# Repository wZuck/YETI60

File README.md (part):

English | [Chinese](README.zh-CN.md)

# YETI60

> **Active prototype: Raytac MDBT50Q-1MV2.** Start at [START-HERE.md](START-HERE.md) or the [ordering and build handbook](variants/raytac/BUILD.md) for PCB settings, inventory-adjusted materials, soldering, firmware, complete explosion and current review. E73 remains a separate option; see its [current review and build entry](BUILD.md) before using those files. Physical and supplier acceptance remain open.

A single-nRF52840 electrocapacitive keyboard PCB for the FELK60 case, derived from Cipulot EC60. The 60 effective sensing positions and mounts are retained. Raytac retains its RF wing; the E73 corner candidate restores the straight edge and front-mounts the module. C5 feeds USB through J4, with a J5/J1 power bridge.

**Wired operation:** after a computer accepts the USB configuration, the keyboard charges the battery and sends HID input over USB at the same time. USB automatically takes priority over a retained Bluetooth preference; unplugging lets ZMK fall back to the active Bluetooth profile. The E73 and Raytac options use the same policy. The 500 mA descriptor is an input budget, not a constant battery charging current.

> **P2 design checkpoint:** C5 JSH is retained. The default is now a custom 1600 mAh single-cell pack with a canonical recessed bottom, revised charger settings and USB500 firmware. Engineering sheets, PCB animation and assembly renders record their source hashes. See [checkpoint details](docs/design-checkpoint.md).

> **Acceptance hold:** E73 is now in the lower-right HHKB corner. Strict DRC has zero violation errors but zero unconnected items; earlier zero-open and firmware reports do not qualify this placement. See the [current migration review](docs/engineering/e73-hhkb-corner.md). Raytac has a separate [review](variants/raytac/BUILD.md). Neither is a production release.

## Current review

**The E73 corner version has completed native routing; whole-board acceptance remains open.** Start at [BUILD.md](BUILD.md). The results below describe the [corner candidate](docs/engineering/e73-hhkb-corner.md); earlier upper-right acceptance does not transfer.

| Scope | Current evidence and result |
|---|---|
| PCB | Strict DRC: 0 violation errors, zero unconnected items, 0 schematic-parity differences; 60 effective sensing positions and 43 module pad roles retained; fabrication remains on hold |
| Firmware | [Candidate normal/calibrator images and manifest](hardware/e73-hhkb-corner/firmware/manifest.json) rebuilt for this PCB; linked-target and host suite passed; physical tests remain open |
| Mechanical | NiZ, the 1.6 mm steel plate and 28 mounting sets retained; module/local body bounds passed, complete mechanism and harness motion still open |
| Battery | Protected 1S 1600 mAh, complete 85 × 43 × 4.8 mm envelope retained; mainboard uses a three-pin SH connector; supplier parameters and independent thermal protection remain open |
| Visualization | [Current native PCB placement](hardware/e73-hhkb-corner/audit/corner-layout.png); old 28-step guide and complete renders are pre-migration references, not this revision's assembly proof |

The remaining study and step-guide links below retain pre-migration reference records; use the corner reports above for this revision.

- [Internal connections and cable drawing](docs/engineering/interconnects.md)
- [Feasibility assessment response](docs/engineering/assessment-response.md)
- [Ordinary fabrication review package](docs/engineering/fabrication-review.md)
- [Engineering assembly sheets and sequence](docs/engineering/assembly.md)
- [28-step illustrated soldering and installation guide](docs/assembly/build-guide.md)
- [Battery recess feasibility](docs/engineering/battery-study.md)
- [Power, runtime and charging calculation](docs/engineering/power-budget.md)
- [Materials and procurement table](docs/engineering/materials.md)
- [PCB marking cleanup](docs/engineering/board-markings.md)
- [Complete review](docs/audit/yeti60-comprehensive-review.md)
- [Hardware and fabrication notes](hardware/ec60-nrf52840/README.md)
- [Firmware core, simulation and trace](firmware/yeti60/README.md)
- [Assembly renders](renders/yeti60-assembly/README.md)
- [PCB renders and 360° animation](renders/ec60-nrf52840/README.md)
- [Current audit index](docs/audit/README.md)

The case material is provisionally resin. SI/RF screening has started; antenna layout blockers and physical qualification remain open. Project-owned prose defaults to English with a parallel `.zh-CN.md`; machine-readable field names stay stable.

Based on [Cipulot/EC60](https://github.com/Cipulot/EC60) and [fredlb/felk60](https://github.com/fredlb/felk60). Upstream authors, licenses and original project names are retained. Existing `EC60-nRF52840.*` filenames and `YAECKB` library identifiers remain for technical compatibility; the public project name is **YETI60**.

## Complete materials for one keyboard

**E73 design hold:** the list below now uses NiZ, a 1.6 mm plate and 28 mounting sets. USB routing and PH connector service remain unresolved, so mainboard manufacturing is still on hold. Read the [current E73 entry](BUILD.md) first; use the [separate Raytac list](variants/raytac/BUILD.md) for that candidate. Retain the already-made C5 daughterboard.

Quantities below are **net installed quantities for one complete keyboard, without spares**. Buy populated mainboard/daughterboard assemblies or their loose parts; do not count the same components twice. Unselected suppliers/MPNs are identified explicitly. A known quantity does not constitute procurement release.

**Fabrication constraint: JLC ordinary four-layer FR-4 only. The previous blind-via/filled-and-capped design has been converted to mechanically drilled through vias; do not order the old HDI files.** Use the latest fabrication review after conversion. No second controller, per-key diodes or MX hot-swap sockets are required.

### Use existing inventory first

The supplied order-derived inventory covers **8** of the 75 current corner mainboard parts by nominal value/package, leaving **67** to purchase for one keyboard. Count the actual unused stock and qualify capacitor effective capacitance before assembly. In-transit items are excluded. The original workbook is unchanged and is not published.

| Stock MPN | References | Planned use |
|---|---|---:|
| Samsung CL05B104KO5NNNC, 100 nF / 16 V / X7R / 0402 | C9, C11, C12, C31 | 4 |
| Samsung CL05A105KA5NQNC, 1 uF / 25 V / X5R / 0402 | C13, C48 | 2 |
| Uniroyal 0402WGF1001TCE, 1 kohm / 1% / 0402 | R17 | 1 |
| Uniroyal 0402WGF1002TCE, 10 kohm / 1% / 0402 | R26 | 1 |

Use the [stock-adjusted mainboard purchase CSV](hardware/e73-hhkb-corner/mainboard-purchase.csv) and [inventory decisions](docs/engineering/inventory-allocation.md) alongside the full preparation list below. Other assemblies and mechanical materials still require procurement or compatibility confirmation. A populated C5 includes its seven parts; if self-assembling a bare C5 instead, two stocked 5.1 kohm resistors can supply C5 R1/R2. The stock nice!nano, 110 mAh cell, 0805 capacitors and short PCB screws do not directly replace the specified parts. No board or case dimensions change for this allocation.

### Which PCBs to fabricate

Quantities are net boards per keyboard; the fabricator's minimum order quantity is separate. Fabricate **one mainboard** when buying a populated C5, or **one mainboard plus one C5 JSH bare board** when soldering the daughterboard yourself.

| PCB | Quantity | Specification | Files |
|---|---:|---|---|
| YETI60 E73 mainboard | 1 | 285.0 × 94.6 mm restored straight-edge outline; JLC ordinary four-layer FR-4, nominal 1.6 mm, through vias only | [Current KiCad PCB](hardware/e73-hhkb-corner/EC60-nRF52840.kicad_pcb), [migration gates](docs/engineering/e73-hhkb-corner.md); no fabrication package released for this revision; do not substitute old Gerbers |
| Unified Daughterboard C5 JSH | 1 only for self-assembly; 0 if purchased populated | 18.0 x 16.5 mm; **four layers**, nominal 1.6 mm, ordinary through vias; 14 x 12.5 mm mounting rectangle | [Pinned upstream KiCad PCB](https://github.com/Unified-Daughterboard/UDB-C-JSH/blob/2b6c52aa2de6f9f60ca99c6250e4bdf01e8f4eea/UDB.kicad_pcb), [download pinned Gerber/drill ZIP](https://raw.githubusercontent.com/Unified-Daughterboard/UDB-C-JSH/2b6c52aa2de6f9f60ca99c6250e4bdf01e8f4eea/production/UDB-C-JSH_5.0_gerbers.zip), [seven loose parts](hardware/bom/daughterboard.csv) |

No fabrication package is released for this corner mainboard. Do not substitute an old mainboard archive. C5 uses separate, unchanged four-layer files; do not order it as two layers. Reuse the already-made C5. Final stencil and supplier acceptance remain open. J3 is part of the main PCB and needs a pogo fixture, not another PCB in this design. The stainless plate, resin shells and five routing guides are mechanical parts, not additional PCBs. For self-reflow, use mainboard **F.Paste and B.Paste** (E73 on front, other parts on back) and C5 **F.Paste** with a qualified stencil/profile.

### Electronic assemblies, battery and cables

| Material | Quantity | Detailed specification and included items |
|---|---:|---|
| Mainboard PCB | 1 | Current YETI60 native PCB; ordinary four-layer FR-4, target nominal thickness 1.6 mm; preserve EC electrodes and mounting centers; use the restored straight right edge; CAD envelope 1.6062 mm; wait for this revision to be released with matching fabrication files |
| Mainboard fitted parts | 75 | Every reference, value, package and specified/candidate MPN is listed below; included if buying a populated mainboard |
| USB daughterboard | 1 populated | Unified Daughterboard C5 JSH, commit `2b6c52a`; seven fitted components including USB-C receptacle and SH header; retain C rather than S |
| Internal USB harness | 1 four-wire | AWG28 stranded copper, insulation OD ≤0.8 mm; two SHR-04V-S housings and eight SSH-003T-P0.2-H contacts; C5 to J4: 1-to-1 power, 2-to-2 D−, 3-to-3 D+, 4-to-4 GND. Complete new routing remains unqualified; do not cut to the old 150 mm figure |
| J5-to-J1 power bridge | 1 two-wire | AWG28, insulation OD ≤0.8 mm; one SHR-02V-S, one SHR-04V-S and four SSH-003T-P0.2-H contacts; J5.1→J1.1 and J5.2→J1.4, J1.2/J1.3 empty; final lengths and retention remain open |
| Battery assembly | 1 pack | Custom single-cell YETI60-BAT-1600-1S, target minimum 1600 mAh; complete pack <=85 x 43 x 4.8 mm including PCM, sensors, wrap, tabs and growth; independent thermal interruption, actual charging window within 15–43 C; supplier must accept >=500 mA continuous charging capability and the 4.16–4.23 V regulation range |
| Battery leads and plug | 1 three-wire set, included in pack | AWG28, OD <=0.8 mm; one SHR-03V-S housing and three SSH-003T-P0.2-H contacts, mating with SM03B-SRSS-TB at 1.00 mm pitch; pin 1 red positive, 2 black negative, 3 yellow separate 10k NTC. Independent thermal protection and third-wire NTC feedback are separate requirements; supplier-signed envelope/lead-exit drawing required |
| External USB data cable | 1 | USB-C at keyboard; USB-A or USB-C at host as appropriate; data capable, not charge-only |

### Every fitted mainboard component

0402 resistors: 1%, >=50 mW; fit 0-ohm links where specified. The 220 pF capacitor is C0G; others X5R/X7R, 10% or better, >=10 V (16 V where specified), with effective DC-biased capacitance to be qualified. Values below are current circuit requirements; unselected MPNs are not frozen parts.

| References | Quantity | Value/function | Package | Specified/candidate MPN | Planned stock | To buy | Stock and qualification notes |
|---|---:|---|---|---|---:|---:|---|
| C9, C11, C12 | 3 | 100n | C_0402_1005Metric | Samsung CL05B104KO5NNNC | 3 | 0 | In inventory: Samsung CL05B104KO5NNNC; recorded received pool 100 (shared by source row, do not sum per BOM row); count before assembly; qualify effective capacitance |
| C10 | 1 | 220p | C_0402_1005Metric | Vendor MPN unselected | 0 | 1 | No matched usable stock; purchase required |
| C13 | 1 | 1u | C_0402_1005Metric | Samsung CL05A105KA5NQNC | 1 | 0 | In inventory: Samsung CL05A105KA5NQNC; recorded received pool 50 (shared by source row, do not sum per BOM row); count before assembly; qualify effective capacitance |
| C30 | 1 | 10u/10V | C_0603_1608Metric | Vendor MPN unselected | 0 | 1 | No matched usable stock; purchase required |
| C41 | 1 | 22u/10V | C_0805_2012Metric | Vendor MPN unselected | 0 | 1 | No matched usable stock; purchase required; 0805 X5R/X7R; require effective capacitance >= 4.7 uF at 4.23 V including tolerance/temperature/aging; nominal value alone is insufficient. Installed height below local PCB underside <= 1.6 mm including solder/seating; body and placement XY growth <= 0.1 mm per direction; remaining tolerances in local fit guide. |
| C42 | 1 | 22u/10V | C_0805_2012Metric | Vendor MPN unselected | 0 | 1 | No matched usable stock; purchase required; 0805 X5R/X7R; require effective capacitance >= 4.7 uF at 4.5 V including tolerance/temperature/aging; nominal value alone is insufficient. Installed height below local PCB underside <= 1.6 mm including solder/seating; body and placement XY growth <= 0.1 mm per direction; remaining tolerances in local fit guide. |
| C43 | 1 | 22u/10V | C_0805_2012Metric | Vendor MPN unselected | 0 | 1 | No matched usable stock; purchase required; 0805 X5R/X7R; require effective capacitance >= 4.7 uF at 4.5 V including tolerance/temperature/aging; nominal value alone is insufficient. Installed height below local PCB underside <= 1.6 mm including solder/seating; body and placement XY growth <= 0.1 mm per direction; remaining tolerances in local fit guide. |
| C45 | 1 | 22u/10V | C_0805_2012Metric | Vendor MPN unselected | 0 | 1 | No matched usable stock; purchase required; 0805 X5R/X7R; require effective capacitance >= 5 uF at 3.6 V including tolerance/temperature/aging; nominal value alone is insufficient. Installed height below local PCB underside <= 1.6 mm including solder/seating; body and placement XY growth <= 0.1 mm per direction; remaining tolerances in local fit guide. |
| C46 | 1 | 22u/10V | C_0805_2012Metric | Vendor MPN unselected | 0 | 1 | No matched usable stock; purchase required; 0805 X5R/X7R; require effective capacitance >= 5 uF at 3.6 V including tolerance/temperature/aging; nominal value alone is insufficient. Installed height below local PCB underside <= 1.6 mm including solder/seating; body and placement XY growth <= 0.1 mm per direction; remaining tolerances in local fit guide. |
| C31 | 1 | 100n/16V | C_0402_1005Metric | Samsung CL05B104KO5NNNC | 1 | 0 | In inventory: Samsung CL05B104KO5NNNC; recorded received pool 100 (shared by source row, do not sum per BOM row); count before assembly; qualify effective capacitance |
| C32 | 1 | 4.7u/16V | C_0603_1608Metric | Vendor MPN unselected | 0 | 1 | No matched usable stock; purchase required; 0603 X5R/X7R; require effective capacitance >= 2.2 uF at 5.25 V including tolerance/temperature/aging; nominal value alone is insufficient. Installed height below local PCB underside <= 1 mm including solder/seating; body and placement XY growth <= 0.1 mm per direction; remaining tolerances in local fit guide. |
| C40 | 1 | 2.2u/25V | C_0805_2012Metric | Vendor MPN unselected | 0 | 1 | No matched usable stock; purchase required; 0805 X5R/X7R; require effective capacitance >= 1 uF at 5.25 V including tolerance/temperature/aging; nominal value alone is insufficient. Installed height below local PCB underside <= 1.6 mm including solder/seating; body and placement XY growth <= 0.1 mm per direction; remaining tolerances in local fit guide. |
| C44 | 1 | 100n/16V | C_0603_1608Metric | Vendor MPN unselected | 0 | 1 | No matched usable stock; purchase required. Installed height below local PCB underside <= 1 mm including solder/seating; body and placement XY growth <= 0.1 mm per direction; remaining tolerances in local fit guide. |
| C47 | 1 | 10n | C_0402_1005Metric | Vendor MPN unselected | 0 | 1 | No matched usable stock; purchase required |
| C48 | 1 | 1u/10V | C_0402_1005Metric | Samsung CL05A105KA5NQNC | 1 | 0 | In inventory: Samsung CL05A105KA5NQNC; recorded received pool 50 (shared by source row, do not sum per BOM row); count before assembly; qualify effective capacitance |
| D2 | 1 | STATUS | LED_0603_1608Metric | 0603 status LED; vendor MPN unselected | 0 | 1 | No matched usable stock; purchase required |
| F1 | 1 | 1A_FAST_0466001_NRHF | Fuse_Littelfuse_0466_1206 | Littelfuse 0466001.NRHF (1 A fast, not resettable) | 0 | 1 | No matched usable stock; purchase required. Installed height below local PCB underside <= 1.2 mm including solder/seating; body and placement XY growth <= 0.1 mm per direction; remaining tolerances in local fit guide. |
| J1 | 1 | USB_POWER_IN | JST-SR-4 | JST SM04B-SRSS-TB(LF)(SN), candidate | 0 | 1 | No matched usable stock; purchase required |
| J2 | 1 | PROTECTED_1S_4V2_NTC10K | JST SH 1.0 mm side-entry 3-pin | JST SM03B-SRSS-TB(LF)(SN) | 0 | 1 | No matched usable stock; purchase required; SH3 revision: protected PACK+/PACK-/NTC on pins 1/2/3; housing SHR-03V-S. Installed height below local PCB underside <= 3.2 mm including solder/seating; body and placement XY growth <= 0.1 mm per direction; remaining tolerances in local fit guide. |
| L1 | 1 | 1.5uH_74438336015 | WE-MAPI 3020, 3.0 x 3.0 x 2.0 mm | Wuerth 74438336015 | 0 | 1 | No matched usable stock; purchase required. Installed height below local PCB underside <= 2.2 mm including solder/seating; body and placement XY growth <= 0.1 mm per direction; remaining tolerances in local fit guide. |
| R3 | 1 | 100 | R_0402_1005Metric | Vendor MPN unselected | 0 | 1 | No matched usable stock; purchase required |
| R4 | 1 | 100 | R_0402_1005Metric | Vendor MPN unselected | 0 | 1 | No matched usable stock; purchase required |
| R5 | 1 | 100 | R_0402_1005Metric | Vendor MPN unselected | 0 | 1 | No matched usable stock; purchase required |
| R6 | 1 | 100 | R_0402_1005Metric | Vendor MPN unselected | 0 | 1 | No matched usable stock; purchase required |
| R7 | 1 | 100 | R_0402_1005Metric | Vendor MPN unselected | 0 | 1 | No matched usable stock; purchase required |
| R47 | 1 | 100 | R_0402_1005Metric | Vendor MPN unselected | 0 | 1 | No matched usable stock; purchase required. Installed height below local PCB underside <= 0.6 mm including solder/seating; body and placement XY growth <= 0.1 mm per direction; remaining tolerances in local fit guide. |
| R53 | 1 | 100 | R_0402_1005Metric | Vendor MPN unselected | 0 | 1 | No matched usable stock; purchase required |
| R54 | 1 | 100 | R_0402_1005Metric | Vendor MPN unselected | 0 | 1 | No matched usable stock; purchase required |
| R8 | 1 | 100k | R_0402_1005Metric | Vendor MPN unselected | 0 | 1 | No matched usable stock; purchase required |
| R9 | 1 | 100k | R_0402_1005Metric | Vendor MPN unselected | 0 | 1 | No matched usable stock; purchase required |
| R10 | 1 | 100k | R_0402_1005Metric | Vendor MPN unselected | 0 | 1 | No matched usable stock; purchase required |
| R11 | 1 | 100k | R_0402_1005Metric | Vendor MPN unselected | 0 | 1 | No matched usable stock; purchase required |
| R12 | 1 | 100k | R_0402_1005Metric | Vendor MPN unselected | 0 | 1 | No matched usable stock; purchase required |
| R13 | 1 | 100k | R_0402_1005Metric | Vendor MPN unselected | 0 | 1 | No matched usable stock; purchase required |
| R14 | 1 | 100k | R_0402_1005Metric | Vendor MPN unselected | 0 | 1 | No matched usable stock; purchase required |
| R15 | 1 | 100k | R_0402_1005Metric | Vendor MPN unselected | 0 | 1 | No matched usable stock; purchase required |
| R16 | 1 | 100k | R_0402_1005Metric | Vendor MPN unselected | 0 | 1 | No matched usable stock; purchase required |
| R18 | 1 | 100k | R_0402_1005Metric | Vendor MPN unselected | 0 | 1 | No matched usable stock; purchase required |
| R19 | 1 | 100k | R_0402_1005Metric | Vendor MPN unselected | 0 | 1 | No matched usable stock; purchase required |
| R20 | 1 | 100k | R_0402_1005Metric | Vendor MPN unselected | 0 | 1 | No matched usable stock; purchase required |
| R21 | 1 | 100k | R_0402_1005Metric | Vendor MPN unselected | 0 | 1 | No matched usable stock; purchase required |
| R23 | 1 | 100k | R_0402_1005Metric | Vendor MPN unselected | 0 | 1 | No matched usable stock; purchase required |
| R24 | 1 | 100k | R_0402_1005Metric | Vendor MPN unselected | 0 | 1 | No matched usable stock; purchase required |
| R25 | 1 | 100k | R_0402_1005Metric | Vendor MPN unselected | 0 | 1 | No matched usable stock; purchase required |
| R42 | 1 | 100k | R_0402_1005Metric | Vendor MPN unselected | 0 | 1 | No matched usable stock; purchase required |
| R43 | 1 | 100k | R_0402_1005Metric | Vendor MPN unselected | 0 | 1 | No matched usable stock; purchase required |
| R44 | 1 | 100k | R_0402_1005Metric | Vendor MPN unselected | 0 | 1 | No matched usable stock; purchase required |
| R45 | 1 | 100k | R_0402_1005Metric | Vendor MPN unselected | 0 | 1 | No matched usable stock; purchase required. Installed height below local PCB underside <= 0.6 mm including solder/seating; body and placement XY growth <= 0.1 mm per direction; remaining tolerances in local fit guide. |
| R46 | 1 | 100k | R_0402_1005Metric | Vendor MPN unselected | 0 | 1 | No matched usable stock; purchase required. Installed height below local PCB underside <= 0.6 mm including solder/seating; body and placement XY growth <= 0.1 mm per direction; remaining tolerances in local fit guide. |
| R48 | 1 | 100k | R_0402_1005Metric | Vendor MPN unselected | 0 | 1 | No matched usable stock; purchase required |
| R49 | 1 | 100k | R_0402_1005Metric | Vendor MPN unselected | 0 | 1 | No matched usable stock; purchase required |
| R50 | 1 | 100k | R_0402_1005Metric | Vendor MPN unselected | 0 | 1 | No matched usable stock; purchase required |
| R17 | 1 | 1k | R_0402_1005Metric | Uniroyal 0402WGF1001TCE | 1 | 0 | In inventory: Uniroyal 0402WGF1001TCE; recorded received pool 100 (shared by source row, do not sum per BOM row); count before assembly |
| R26 | 1 | 10k | R_0402_1005Metric | Uniroyal 0402WGF1002TCE | 1 | 0 | In inventory: Uniroyal 0402WGF1002TCE; recorded received pool 100 (shared by source row, do not sum per BOM row); count before assembly |
| R32 | 1 | 2.2k | R_0402_1005Metric | Vendor MPN unselected | 0 | 1 | No matched usable stock; purchase required |
| R40 | 1 | 2.21k/1% | R_0402_1005Metric | Vendor MPN unselected | 0 | 1 | No matched usable stock; purchase required |
| R41 | 1 | 7.50k/1% | R_0402_1005Metric | Vendor MPN unselected | 0 | 1 | No matched usable stock; purchase required |
| R51, R52 | 2 | 1M/1% | R_0402_1005Metric | Vendor MPN unselected | 0 | 2 | No matched usable stock; purchase required |
| R55 | 1 | 69.8k/1% | R_0402_1005Metric | Vendor MPN unselected | 0 | 1 | No matched usable stock; purchase required |
| R56 | 1 | 1.69k/1% | R_0402_1005Metric | Vendor MPN unselected | 0 | 1 | No matched usable stock; purchase required |
| SW1 | 1 | EVQPUC02K_RESET | Panasonic_EVQPUL_EVQPUC | Panasonic EVQPUC02K | 0 | 1 | No matched usable stock; purchase required |
| SW100 | 1 | JS102011SAQN_POWER | SW_SPDT_CK_JS102011SAQN | C&K JS102011SAQN | 0 | 1 | No matched usable stock; purchase required |
| U1 | 1 | E73-2G4M08S1C | E73-2G4M08S1C | Ebyte E73-2G4M08S1C | 0 | 1 | No matched usable stock; purchase required |
| U2, U4 | 2 | 74HC4051 | TSSOP16 | Nexperia 74HC4051PW,118 | 0 | 2 | No matched usable stock; purchase required |
| U3 | 1 | OPA350 | SOIC-8_3.9x4.9mm_P1.27mm | TI OPA350UA | 0 | 1 | No matched usable stock; purchase required |
| U5 | 1 | BQ24074RGT | VQFN-16-1EP_3x3mm_P0.5mm_EP1.6x1.6mm | TI BQ24074RGTR | 0 | 1 | No matched usable stock; purchase required. Installed height below local PCB underside <= 1.2 mm including solder/seating; body and placement XY growth <= 0.1 mm per direction; remaining tolerances in local fit guide. |
| U6 | 1 | TPS63031DSK | WSON-10-1EP_2.5x2.5mm_P0.5mm_EP1.2x2mm | TI TPS63031DSKR | 0 | 1 | No matched usable stock; purchase required. Installed height below local PCB underside <= 1 mm including solder/seating; body and placement XY growth <= 0.1 mm per direction; remaining tolerances in local fit guide. |
| U7, U8 | 2 | TPS22919DCK | SOT-363_SC-70-6 | TI TPS22919DCKR | 0 | 2 | No matched usable stock; purchase required |
| J4 | 1 | USB_C5_INPUT | JST SH 1.0 mm side-entry 4-pin | JST SM04B-SRSS-TB(LF)(SN) | 0 | 1 | No inventory credit; USB repair candidate, fabrication release still on hold. Installed height below local PCB underside <= 3.2 mm including solder/seating; body and placement XY growth <= 0.1 mm per direction; remaining tolerances in local fit guide. |
| J5 | 1 | USB_POWER_OUT | JST SH 1.0 mm side-entry 2-pin | JST SM02B-SRSS-TB(LF)(SN) | 0 | 1 | No inventory credit; USB repair candidate, fabrication release still on hold. Installed height below local PCB underside <= 3.2 mm including solder/seating; body and placement XY growth <= 0.1 mm per direction; remaining tolerances in local fit guide. |

### Optional: solder a bare C5 JSH daughterboard

Prepare **one bare C5 JSH PCB and the seven parts below** instead of buying a populated C5. [Local stock-adjusted CSV](hardware/bom/daughterboard.csv) · [Pinned upstream BOM](https://github.com/Unified-Daughterboard/UDB-C-JSH/blob/2b6c52aa2de6f9f60ca99c6250e4bdf01e8f4eea/production/UDB-C-JSH_5.0_bom.csv) · [Pinned upstream Gerber archive](https://github.com/Unified-Daughterboard/UDB-C-JSH/blob/2b6c52aa2de6f9f60ca99c6250e4bdf01e8f4eea/production/UDB-C-JSH_5.0_gerbers.zip).

| References | Quantity | Manufacturer and specified MPN | Package / connector footprint | LCSC code | Planned stock use | To buy | Inventory note |
| --- | --- | --- | --- | --- | --- | --- | --- |
| D1 | 1 | FTR SMF6.0A | SOD-123FL | C708002 | 0 | 1 | No matched usable stock; purchase required |
| F1 | 1 | Shenzhen JDT Fuse ASMD1206-150 | F1206 | C135342 | 0 | 1 | No matched usable stock; purchase required |
| J2 | 1 | JST SM04B-SRSS-TB(LF)(SN) | SM04B-SRSS-TB(LF)(SN)_mounting-reliefs | C160404 | 0 | 1 | No matched usable stock; purchase required |
| J1 | 1 | Korean Hroparts TYPE-C-31-M-12 | TYPE-C-31-M-12 | C165948 | 0 | 1 | 6 domestic substitutes recorded received; geometry/pinout unconfirmed, no credit |
| R1, R2 | 2 | Uniroyal 0402WGF5101TCE | R0402 | C25905 | 2 | 0 | Matching stock; recorded received pool 100, plan to use 2; count before assembly |
| U1 | 1 | Texas Instruments TPD4E05U06DQAR | uSON-10 | C138714 | 0 | 1 | No matched usable stock; purchase required |

The stock 5.1 kohm resistors cover R1/R2, so this option needs **five more loose parts plus one bare PCB**. The stock domestic TYPE-C-31-M-12 is not credited until its geometry is confirmed. These are daughterboard reference numbers, separate from mainboard references. The USB harness, four M2 screws and washers are separate assembly items below. LCSC codes identify the pinned upstream entries, not current prices or stock guarantees. BOM data: Copyright (c) 2023 Unified Daughterboard Project, [MIT license](hardware/usb-daughterboard/LICENSE.upstream).

### Case, EC mechanism and fasteners

| ID | Material | Quantity | Detailed specification/acceptance |
|---|---|---:|---|
| M01 | Top shell | 1 | Derived FELK60 HHKB STEP, tough SLA resin, post-cured; no exterior scaling |
| M02 | Bottom shell | 1 | Selected [E73 M01 STEP](mechanical/e73-fit/yeti60-e73-bottom-m01.step), P2 1600 mAh recess and SW100 floor relief; original exterior |
| M03 | Plate | 1 | K07 E73 M01 NiZ plate-mount DXF, 304 stainless, CAD thickness 1.60 mm, finished 1.55-1.60 mm, 28 M2 x 0.4 axes; no H26 plate mounting hole |
| M04 | NiZ housings / sliders / original rings | 60 | K01 five per pack, buy 13 packs / 65; install 60, spare 5; ordinary center housings for big keys, no Deskeys wide assembly |
| M05 | Rubber domes | 60 positions | K03 NiZ 45g sheet, one sheet; use 60 complete positions trimmed for HHKB; not included in K01 |
| M06 | Conical EC springs | 60 | K02 NiZ five per pack, buy 13 packs / 65; install 60, spare 5; not helper springs |
| M07 | Plate-mounted stabilizers / wires | 1 matched set | K04 genuine GMK Plate mount / 2u, three sets / six side units; use two short wires and separate K05 6U wire, spare one short wire |
| M08 | Keycaps | 60 | K06 NicePBT BoW current complete kit, one kit including 6.0c Centered spacebar; MX mounts |
| M09 | Adapter standoffs | 28 | YETI60-STANDOFF-46, brass OD3.5, shoulder 4.50 +/-0.03; top M2 x0.4 stud 1.0; bottom M1.6 x0.35 female depth 3.2; H26 unused |
| M10 | Top insulating films | 28 | Polyimide 0.10 +/-0.02 mm, OD4.5 / ID1.8; between standoff and PCB; H26 unused |
| M11 | PCB screws | 28 | M1.6 x5 pan head; verify actual head/thread; H26 unused |
| M12 | PCB washers | 28 | PEEK OD <=4.0, ID2.2, thickness0.8 mm; H26 unused; no conductive metal substitution |
| M13 | Top-shell inserts | 4 | Cold-bonded knurled brass M3×0.5, OD 4.6, length 3.0; bores Ø4.85±0.05, depth 3.5 |
| M14 | Daughterboard inserts | 4 | Cold-bonded brass M2×0.4, OD 3.2, length 2.5; bores Ø3.35±0.05, depth 2.9 |
| M15 | Shell closure screws | 4 | M3×5 with 0.30 mm shim washer; proposed from CAD seat z=2.59 and insert entry z=4.79; nominal engagement 2.50 mm, verify head Ø≤5.6 in Ø5.8 recess |
| M16 | Daughterboard screws | 4 | M2×4 with 0.30 mm insulating washer; nominal thread engagement 4−1.6062−0.30=2.0938 mm in 2.5 mm insert; head clearance to connector requires check |
| M17 | Gasket stock | 1 set | Four 33 x 3 mm pads per layer; lower stock 2.0 mm, upper 1.2 mm; installed gaps 1.0162 /0.5838 mm; force/creep qualification open |
| M18 | Case feet | 4 | [SKUF silicone feet](https://keeb.io/products/skuf-silicone-rubber-keyboard-feet), 41.8 x 5.8 x 2 mm, 45A, adhesive backed; four approximately 42.2 x 6.2 mm case pockets. One 8-pack leaves four spares |
| M19 | Insert adhesive | As needed | Resin-compatible structural epoxy; cold-bond only, cure per adhesive/resin supplier, keep thread bores clear |
| M20 | Battery retention and insulation | 1 set | Nonconductive removable retention and edge protection; include tape thickness in the pocket budget; do not clamp the pouch |

**The selected mechanism is NiZ plus plate-mounted stabilizers.** Use the [E73 mechanism specification](docs/build/key-mechanism.md), including the 6U wire datum, 28 mounting sets and H26 omission. Supplier plastic dimensions, retention, dome preload and full travel require local samples before metal-part production.

### Additional retention parts and consumables

| Material | Quantity | Specification/inclusion |
|---|---:|---|
| Shell screw shims | 4 | 0.30 mm thick, M3 clearance, used with the four M3 x 5 screws above; OD must fit the screw seat |
| Daughterboard insulating washers | 4 | 0.30 mm thick, M2 clearance, for four M2 x 4 screws |
| Rear harness guide bases | 2 | One each of `mechanical/generated/interconnect-guides/rear-1-base` and `rear-2-base` STEP/STL; current width 5.4 and route-direction length 2 mm |
| Rear removable bridges | 2 | One each of `rear-1-bridge` and `rear-2-bridge`; three lower battery wires/four upper USB wires, groove radius 0.5 mm |
| Front USB guide | 1 | `front-base` STEP/STL, width 6 and route-direction length 1.8 mm; install in case coordinates without scaling |
| Polyimide insulation stock | 1 sheet | At least 100 x 100 x 0.10 mm; supplies the 28 insulating discs; do not double-count pre-cut parts. Upper harness retention uses the separately listed adhesive-backed film |
| Gasket stock | 2 sheets | One >=150 x 50 x 2.0 mm lower sheet and one >=150 x 50 x 1.2 mm upper sheet; cut four 33 x 3 mm pads from each. Replaces M17 stock allowance; force/creep and adhesive qualification open |
| Resin-compatible structural adhesive | 1 small two-part kit | For inserts and guides; qualify and cure per adhesive/resin suppliers; quantity denotes a purchase package, not measured consumption |
| Removable battery tape and edge insulation | 1 set | Nominal pack-to-pocket-floor space is only 0.20 mm; tape, insulation and assembly allowance must fit that total budget; do not compress the pouch |
| Upper harness retention tape | 1 small roll, cut 3 pieces | Adhesive-backed insulating film/tape, total thickness <=0.10 mm including adhesive; wrap over the upper wires and down the guide sides |
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
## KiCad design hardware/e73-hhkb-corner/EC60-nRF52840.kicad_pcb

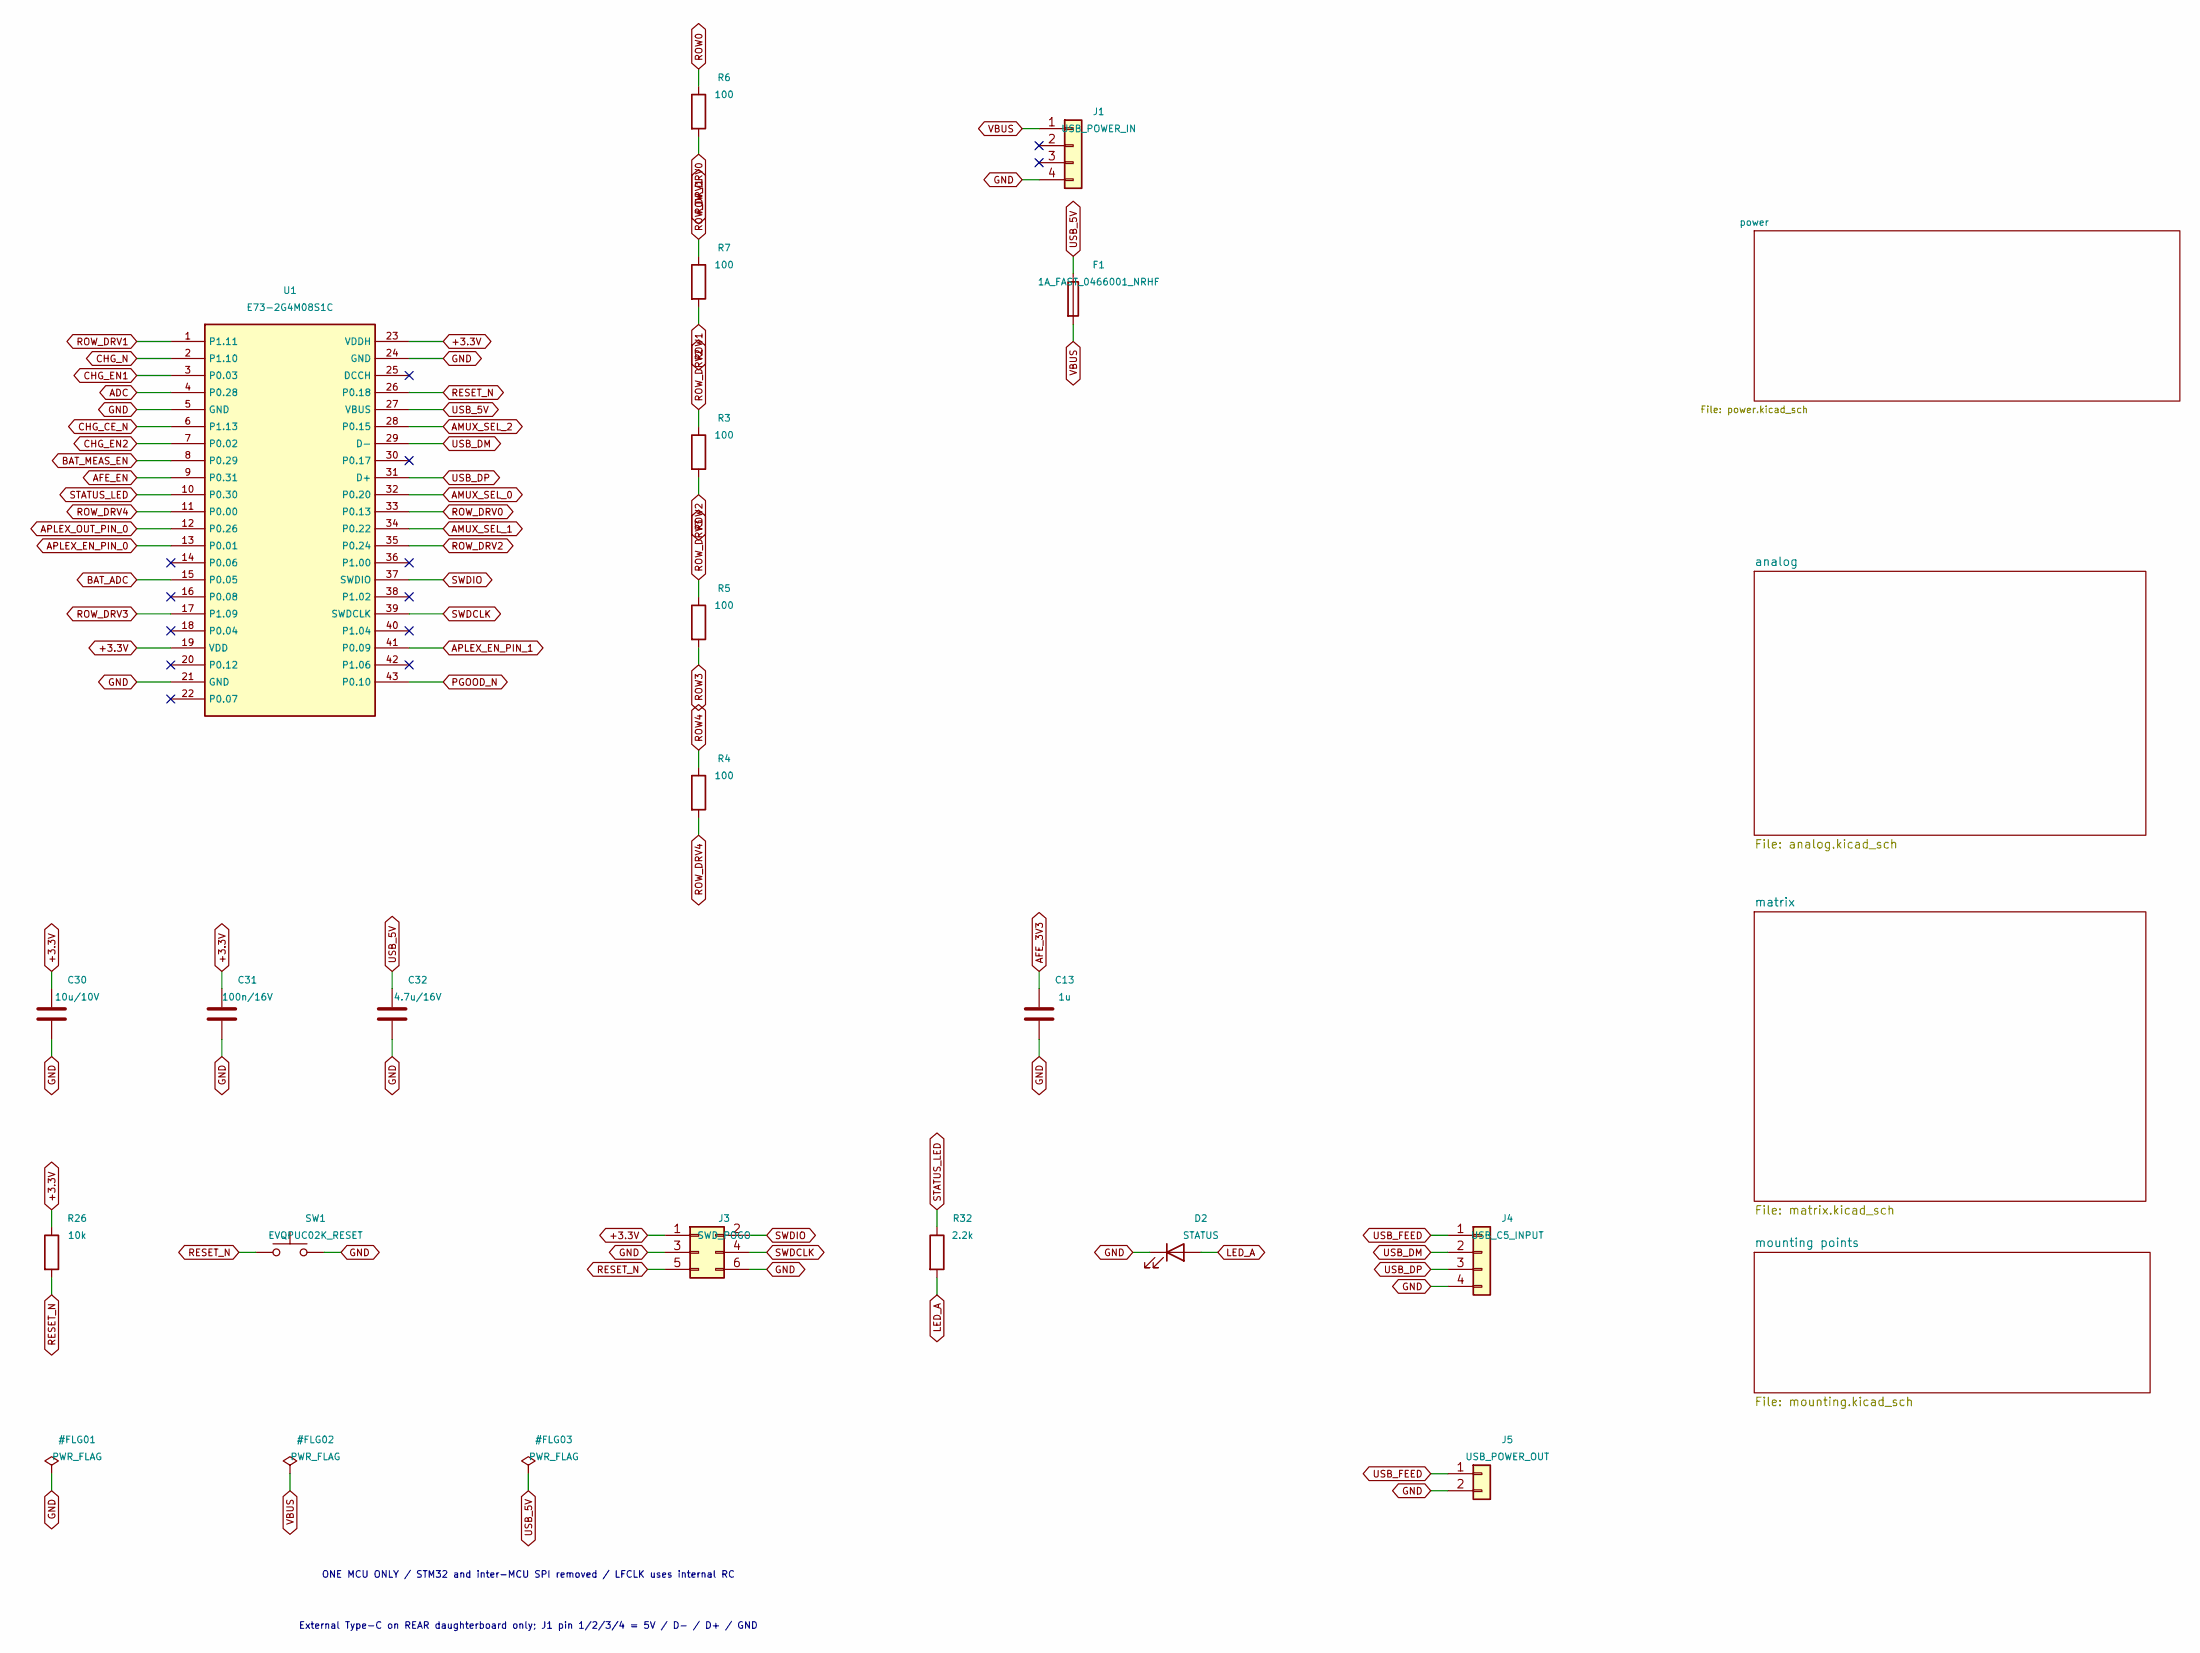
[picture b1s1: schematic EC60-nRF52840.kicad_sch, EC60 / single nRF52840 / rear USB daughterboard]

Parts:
C13: 1u; C_0402_1005Metric__C13
C30: 10u/10V; C_0603_1608Metric__C30
C31: 100n/16V; C_0402_1005Metric__C31
C32: 4.7u/16V; C_0603_1608Metric__C32
D2: STATUS; LED_0603_1608Metric__D2
F1: 1A_FAST_0466001_NRHF; Fuse_Littelfuse_0466_1206__F1
J1: USB_POWER_IN; JST-SR-4__J1
J3: SWD_POGO; SWD_Pogo_2x03__J3
J4: USB_C5_INPUT; JST-SR-4__J4
J5: USB_POWER_OUT; JST_SH_SM02B_SRSS_TB__J5
R3: 100; R_0402_1005Metric__R3
R4: 100; R_0402_1005Metric__R4
R5: 100; R_0402_1005Metric__R5
R6: 100; R_0402_1005Metric__R6
R7: 100; R_0402_1005Metric__R7
R26: 10k; R_0402_1005Metric__R26
R32: 2.2k; R_0402_1005Metric__R32
SW1: EVQPUC02K_RESET; Panasonic_EVQPUL_EVQPUC__SW1
U1: E73-2G4M08S1C; E73-2G4M08S1C__U1

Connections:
+3.3V: C30.1, C31.1, J3.1, R26.1, U1.19 (VDD), U1.23 (VDDH); also elsewhere on the board
ADC: U1.4 (P0.28); also elsewhere on the board
AFE_EN: U1.9 (P0.31); also elsewhere on the board
AMUX_SEL_0: U1.32 (P0.20); also elsewhere on the board
AMUX_SEL_1: U1.34 (P0.22); also elsewhere on the board
AMUX_SEL_2: U1.28 (P0.15); also elsewhere on the board
APLEX_EN_PIN_0: U1.13 (P0.01); also elsewhere on the board
APLEX_EN_PIN_1: U1.41 (P0.09); also elsewhere on the board
APLEX_OUT_PIN_0: U1.12 (P0.26); also elsewhere on the board
BAT_ADC: U1.15 (P0.05); also elsewhere on the board
BAT_MEAS_EN: U1.8 (P0.29); also elsewhere on the board
CHG_CE_N: U1.6 (P1.13); also elsewhere on the board
CHG_EN1: U1.3 (P0.03); also elsewhere on the board
CHG_EN2: U1.7 (P0.02); also elsewhere on the board
CHG_N: U1.2 (P1.10); also elsewhere on the board
GND: C13.2, C30.2, C31.2, C32.2, D2.1 (K), J1.4, J3.3, J3.6, J4.4, J5.2, SW1.2, U1.5 (GND), U1.21 (GND), U1.24 (GND); also elsewhere on the board
LED_A: D2.2 (A), R32.2
PGOOD_N: U1.43 (P0.10); also elsewhere on the board
RESET_N: J3.5, R26.2, SW1.1, U1.26 (P0.18)
ROW0: R6.1; also elsewhere on the board
ROW1: R7.2; also elsewhere on the board
ROW2: R3.2; also elsewhere on the board
ROW3: R5.2; also elsewhere on the board
ROW4: R4.1; also elsewhere on the board
ROW_DRV0: R6.2, U1.33 (P0.13)
ROW_DRV1: R7.1, U1.1 (P1.11)
ROW_DRV2: R3.1, U1.35 (P0.24)
ROW_DRV3: R5.1, U1.17 (P1.09)
ROW_DRV4: R4.2, U1.11 (P0.00)
STATUS_LED: R32.1, U1.10 (P0.30)
SWDCLK: J3.4, U1.39 (SWDCLK)
SWDIO: J3.2, U1.37 (SWDIO)
USB_5V: C32.1, F1.1, U1.27 (VBUS); also elsewhere on the board
USB_DM: J4.2, U1.29 (D-)
USB_DP: J4.3, U1.31 (D+)
USB_FEED: J4.1, J5.1
VBUS: F1.2, J1.1

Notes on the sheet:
ONE MCU ONLY / STM32 and inter-MCU SPI removed / LFCLK uses internal RC
External Type-C on REAR daughterboard only; J1 pin 1/2/3/4 = 5V / D- / D+ / GND

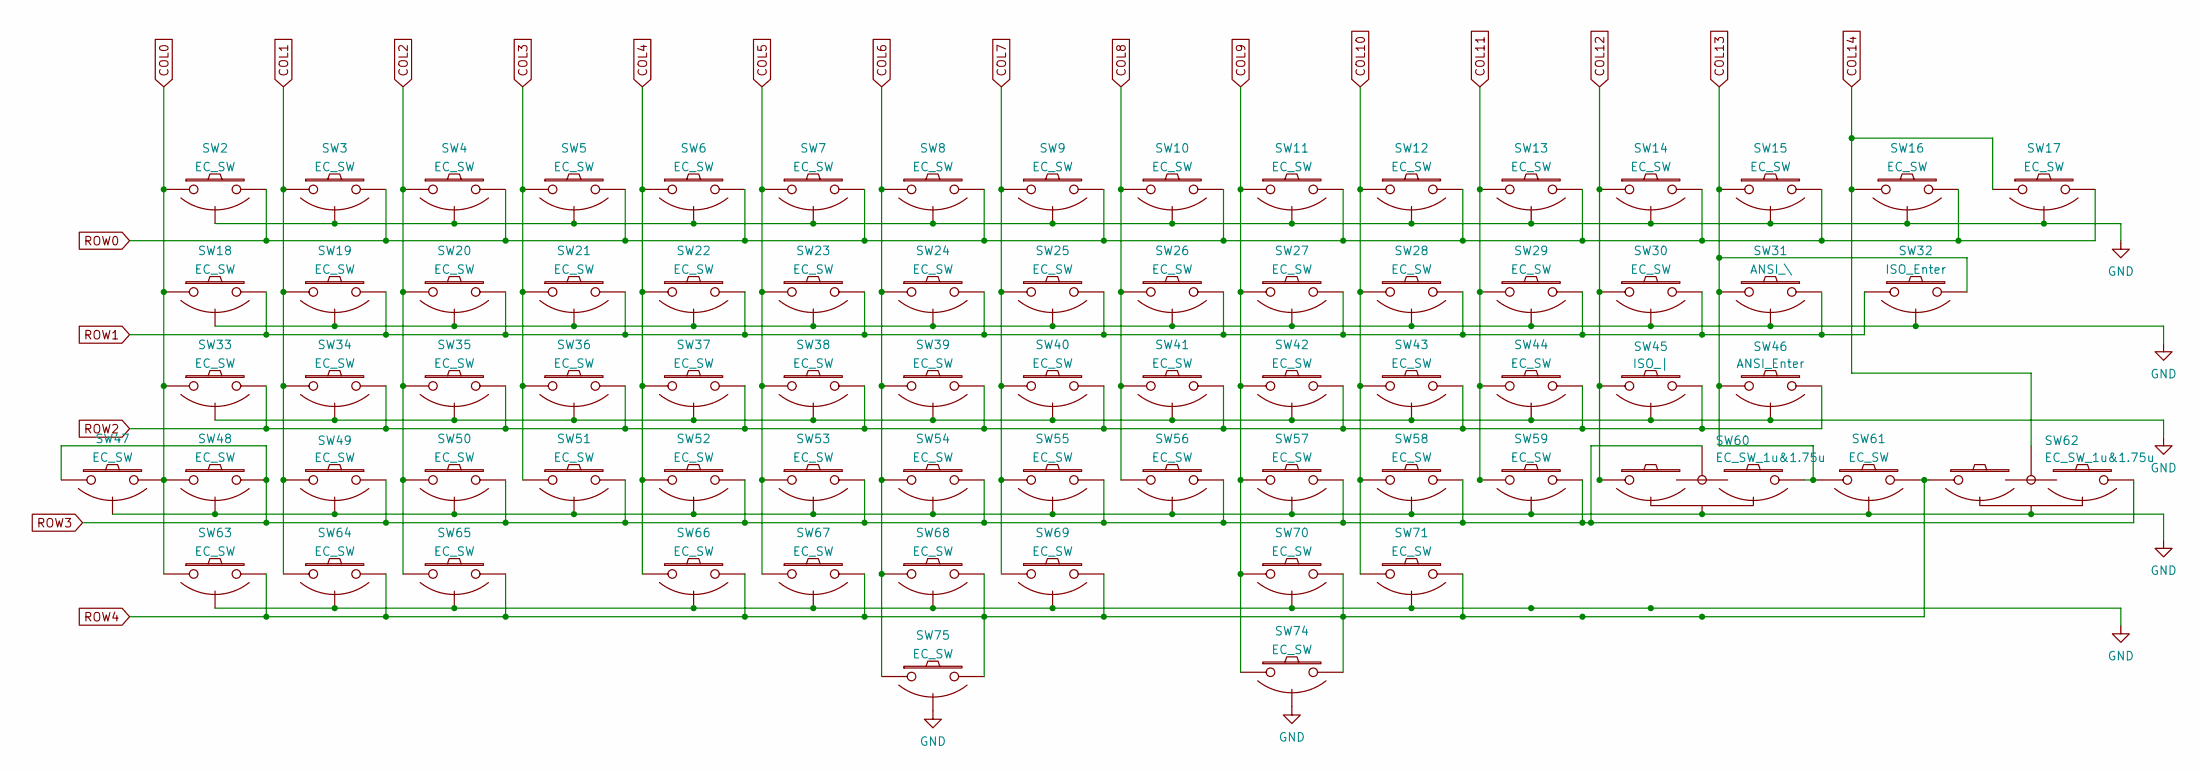
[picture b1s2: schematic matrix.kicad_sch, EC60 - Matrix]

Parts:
SW2: EC_SW; ecs_pad_no_ring__SW2
SW3: EC_SW; ecs_pad_no_ring__SW3
SW4: EC_SW; ecs_pad_no_ring__SW4
SW5: EC_SW; ecs_pad_no_ring__SW5
SW6: EC_SW; ecs_pad_no_ring__SW6
SW7: EC_SW; ecs_pad_no_ring__SW7
SW8: EC_SW; ecs_pad_no_ring__SW8
SW9: EC_SW; ecs_pad_no_ring__SW9
SW10: EC_SW; ecs_pad_no_ring__SW10
SW11: EC_SW; ecs_pad_no_ring__SW11
SW12: EC_SW; ecs_pad_no_ring__SW12
SW13: EC_SW; ecs_pad_no_ring__SW13
SW14: EC_SW; ecs_pad_no_ring__SW14
SW15: EC_SW; ecs_pad_no_ring__SW15
SW16: EC_SW; ecs_pad_no_ring__SW16
SW17: EC_SW; ecs_pad_no_ring__SW17
SW18: EC_SW; ecs_pad_no_ring__SW18
SW19: EC_SW; ecs_pad_no_ring__SW19
SW20: EC_SW; ecs_pad_no_ring__SW20
SW21: EC_SW; ecs_pad_no_ring__SW21
SW22: EC_SW; ecs_pad_no_ring__SW22
SW23: EC_SW; ecs_pad_no_ring__SW23
SW24: EC_SW; ecs_pad_no_ring__SW24
SW25: EC_SW; ecs_pad_no_ring__SW25
SW26: EC_SW; ecs_pad_no_ring__SW26
SW27: EC_SW; ecs_pad_no_ring__SW27
SW28: EC_SW; ecs_pad_no_ring__SW28
SW29: EC_SW; ecs_pad_no_ring__SW29
SW30: EC_SW; ecs_pad_no_ring__SW30
SW31: ANSI_\; ecs_pad_no_ring__SW31
SW32: ISO_Enter; ecs_pad_no_ring__SW32
SW33: EC_SW; ecs_pad_no_ring_stepped&normal__SW33
SW34: EC_SW; ecs_pad_no_ring__SW34
SW35: EC_SW; ecs_pad_no_ring__SW35
SW36: EC_SW; ecs_pad_no_ring__SW36
SW37: EC_SW; ecs_pad_no_ring__SW37
SW38: EC_SW; ecs_pad_no_ring__SW38
SW39: EC_SW; ecs_pad_no_ring__SW39
SW40: EC_SW; ecs_pad_no_ring__SW40
SW41: EC_SW; ecs_pad_no_ring__SW41
SW42: EC_SW; ecs_pad_no_ring__SW42
SW43: EC_SW; ecs_pad_no_ring__SW43
SW44: EC_SW; ecs_pad_no_ring__SW44
SW45: ISO_|; ecs_pad_no_ring__SW45
SW46: ANSI_Enter; ecs_pad_no_ring__SW46
SW47: EC_SW; ecs_pad_no_ring__SW47
SW48: EC_SW; ecs_pad_no_ring_1u_edge_cut__SW48
SW49: EC_SW; ecs_pad_no_ring_1u_edge_cut__SW49
SW50: EC_SW; ecs_pad_no_ring__SW50
SW51: EC_SW; ecs_pad_no_ring__SW51
SW52: EC_SW; ecs_pad_no_ring__SW52
SW53: EC_SW; ecs_pad_no_ring__SW53
SW54: EC_SW; ecs_pad_no_ring__SW54
SW55: EC_SW; ecs_pad_no_ring__SW55
SW56: EC_SW; ecs_pad_no_ring__SW56
SW57: EC_SW; ecs_pad_no_ring__SW57
SW58: EC_SW; ecs_pad_no_ring__SW58
SW59: EC_SW; ecs_pad_no_ring__SW59
SW60: EC_SW_1u&1.75u; ecs_pad_no_ring_1u1.75u__SW60
SW61: EC_SW; ecs_pad_no_ring__SW61
SW62: EC_SW_1u&1.75u; ecs_pad_no_ring_1u1.75u__SW62
SW63: EC_SW; ecs_pad_no_ring__SW63
SW64: EC_SW; ecs_pad_no_ring__SW64
SW65: EC_SW; ecs_pad_no_ring__SW65
SW66: EC_SW; ecs_pad_no_ring__SW66
SW67: EC_SW; ecs_pad_no_ring__SW67
SW68: EC_SW; ecs_pad_no_ring_stepped&normal__SW68
SW69: EC_SW; ecs_pad_no_ring_stepped&normal__SW69
SW70: EC_SW; ecs_pad_no_ring__SW70
SW71: EC_SW; ecs_pad_no_ring_stepped&normal__SW71
SW74: EC_SW; ecs_pad_no_ring__SW74
SW75: EC_SW; ecs_pad_no_ring__SW75

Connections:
COL0: SW2.1, SW18.1, SW33.1, SW47.2, SW48.1, SW63.1; also elsewhere on the board
COL1: SW3.1, SW19.1, SW34.1, SW49.2, SW64.1; also elsewhere on the board
COL2: SW4.1, SW20.1, SW35.1, SW50.1, SW65.1; also elsewhere on the board
COL3: SW5.1, SW21.1, SW36.1, SW51.1; also elsewhere on the board
COL4: SW6.1, SW22.1, SW37.1, SW52.1, SW66.1; also elsewhere on the board
COL5: SW7.1, SW23.1, SW38.1, SW53.1, SW67.1; also elsewhere on the board
COL6: SW8.1, SW24.1, SW39.1, SW54.1, SW68.1, SW75.1; also elsewhere on the board
COL7: SW9.1, SW25.1, SW40.1, SW55.1, SW69.1; also elsewhere on the board
COL8: SW10.1, SW26.1, SW41.1, SW56.1; also elsewhere on the board
COL9: SW11.1, SW27.1, SW42.1, SW57.1, SW70.1, SW74.1; also elsewhere on the board
COL10: SW12.1, SW28.1, SW43.1, SW58.1, SW71.1; also elsewhere on the board
COL11: SW13.1, SW29.1, SW44.1, SW59.1; also elsewhere on the board
COL12: SW14.1, SW30.1, SW45.1, SW60.1; also elsewhere on the board
COL13: SW15.1, SW31.1, SW32.2, SW46.2, SW60.3, SW61.1; also elsewhere on the board
COL14: SW16.1, SW17.1, SW62.2; also elsewhere on the board
GND: SW2.3 (SG), SW3.3 (SG), SW4.3 (SG), SW5.3 (SG), SW6.3 (SG), SW7.3 (SG), SW8.3 (SG), SW9.3 (SG), SW10.3 (SG), SW11.3 (SG), SW12.3 (SG), SW13.3 (SG), SW14.3 (SG), SW15.3 (SG), SW16.3 (SG), SW17.3 (SG), SW18.3 (SG), SW19.3 (SG), SW20.3 (SG), SW21.3 (SG), SW22.3 (SG), SW23.3 (SG), SW24.3 (SG), SW25.3 (SG), SW26.3 (SG), SW27.3 (SG), SW28.3 (SG), SW29.3 (SG), SW30.3 (SG), SW31.3 (SG), SW32.3 (SG), SW33.3 (SG), SW34.3 (SG), SW35.3 (SG), SW36.3 (SG), SW37.3 (SG), SW38.3 (SG), SW39.3 (SG), SW40.3 (SG), SW41.3 (SG), SW42.3 (SG), SW43.3 (SG), SW44.3 (SG), SW45.3 (SG), SW46.3 (SG), SW47.3 (SG), SW48.3 (SG), SW49.3 (SG), SW50.3 (SG), SW51.3 (SG), SW52.3 (SG), SW53.3 (SG), SW54.3 (SG), SW55.3 (SG), SW56.3 (SG), SW57.3 (SG), SW58.3 (SG), SW59.3 (SG), SW60.4 (SG), SW61.3 (SG), SW62.4 (SG), SW63.3 (SG), SW64.3 (SG), SW65.3 (SG), SW66.3 (SG), SW67.3 (SG), SW68.3 (SG), SW69.3 (SG), SW70.3 (SG), SW71.3 (SG), SW74.3 (SG), SW75.3 (SG); also elsewhere on the board
ROW0: SW2.2, SW3.2, SW4.2, SW5.2, SW6.2, SW7.2, SW8.2, SW9.2, SW10.2, SW11.2, SW12.2, SW13.2, SW14.2, SW15.2, SW16.2, SW17.2; also elsewhere on the board
ROW1: SW18.2, SW19.2, SW20.2, SW21.2, SW22.2, SW23.2, SW24.2, SW25.2, SW26.2, SW27.2, SW28.2, SW29.2, SW30.2, SW31.2, SW32.1; also elsewhere on the board
ROW2: SW33.2, SW34.2, SW35.2, SW36.2, SW37.2, SW38.2, SW39.2, SW40.2, SW41.2, SW42.2, SW43.2, SW44.2, SW45.2, SW46.1; also elsewhere on the board
ROW3: SW47.1, SW48.2, SW49.1, SW50.2, SW51.2, SW52.2, SW53.2, SW54.2, SW55.2, SW56.2, SW57.2, SW58.2, SW59.2, SW60.2, SW62.3; also elsewhere on the board
ROW4: SW61.2, SW62.1, SW63.2, SW64.2, SW65.2, SW66.2, SW67.2, SW68.2, SW69.2, SW70.2, SW71.2, SW74.2, SW75.2; also elsewhere on the board

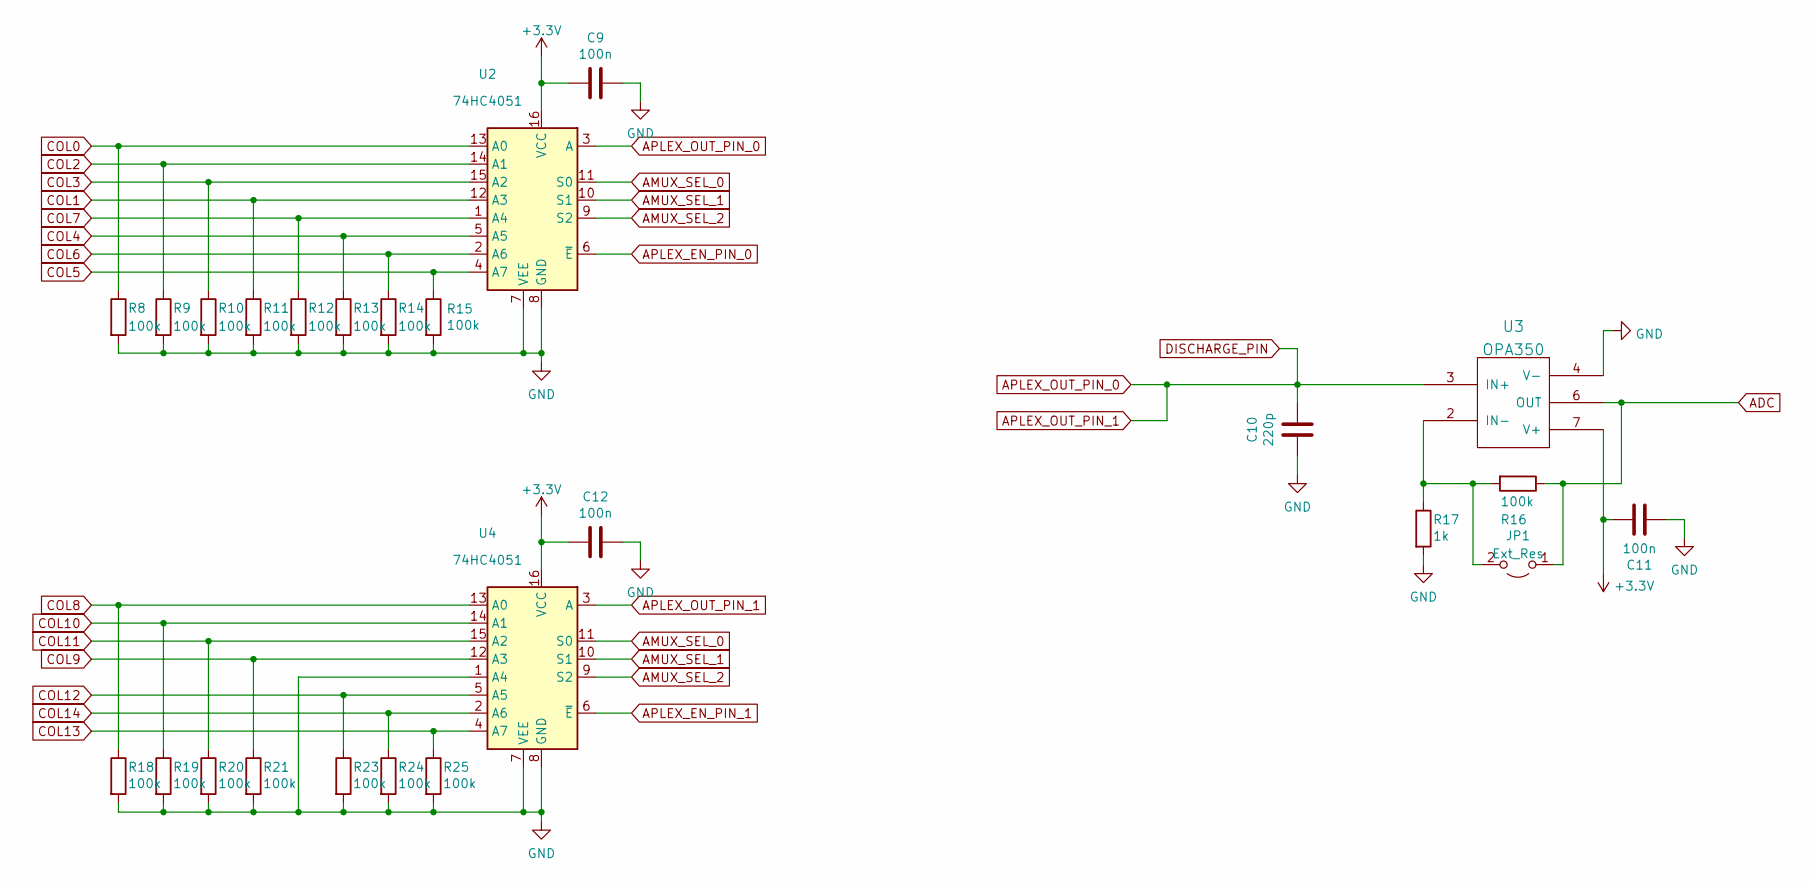
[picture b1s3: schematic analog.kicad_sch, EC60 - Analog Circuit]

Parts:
C9, C11, C12: 100n; C_0402_1005Metric; LCSC C307331
C10: 220p; C_0402_1005Metric; LCSC C1530
JP1: Ext_Res; R_0603_1608Metric_Pad0.98x0.95mm_HandSolder
R8, R9, R10, R11, R12, R13, R14, R15, R16, R18, R19, R20, R21, R23, R24, R25: 100k; R_0402_1005Metric; LCSC C25741
R17: 1k; R_0402_1005Metric; LCSC C11702
U2, U4: 74HC4051; TSSOP16; LCSC C5645
U3: OPA350; SOIC-8_3.9x4.9mm_P1.27mm; LCSC C13388

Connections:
ADC: JP1.1 (A), R16.1, U3.6 (OUT); also elsewhere on the board
AMUX_SEL_0: U2.11 (S0), U4.11 (S0); also elsewhere on the board
AMUX_SEL_1: U2.10 (S1), U4.10 (S1); also elsewhere on the board
AMUX_SEL_2: U2.9 (S2), U4.9 (S2); also elsewhere on the board
APLEX_EN_PIN_0: U2.6 (~E); also elsewhere on the board
APLEX_EN_PIN_1: U4.6 (~E); also elsewhere on the board
APLEX_OUT_PIN_0: C10.1, U2.3 (A), U3.3 (IN+), U4.3 (A); also elsewhere on the board
COL0: R8.1, U2.13 (A0); also elsewhere on the board
COL1: R11.1, U2.12 (A3); also elsewhere on the board
COL2: R9.1, U2.14 (A1); also elsewhere on the board
COL3: R10.1, U2.15 (A2); also elsewhere on the board
COL4: R13.1, U2.5 (A5); also elsewhere on the board
COL5: R15.1, U2.4 (A7); also elsewhere on the board
COL6: R14.1, U2.2 (A6); also elsewhere on the board
COL7: R12.1, U2.1 (A4); also elsewhere on the board
COL8: R18.1, U4.13 (A0); also elsewhere on the board
COL9: R21.1, U4.12 (A3); also elsewhere on the board
COL10: R19.1, U4.14 (A1); also elsewhere on the board
COL11: R20.1, U4.15 (A2); also elsewhere on the board
COL12: R23.1, U4.5 (A5); also elsewhere on the board
COL13: R25.1, U4.4 (A7); also elsewhere on the board
COL14: R24.1, U4.2 (A6); also elsewhere on the board
GND: C9.1, C10.2, C11.1, C12.1, R8.2, R9.2, R10.2, R11.2, R12.2, R13.2, R14.2, R15.2, R17.2, R18.2, R19.2, R20.2, R21.2, R23.2, R24.2, R25.2, U2.7 (VEE), U2.8 (GND), U3.4 (V-), U4.1 (A4), U4.7 (VEE), U4.8 (GND); also elsewhere on the board
unnamed: JP1.2 (B), R16.2, R17.1, U3.2 (IN-)

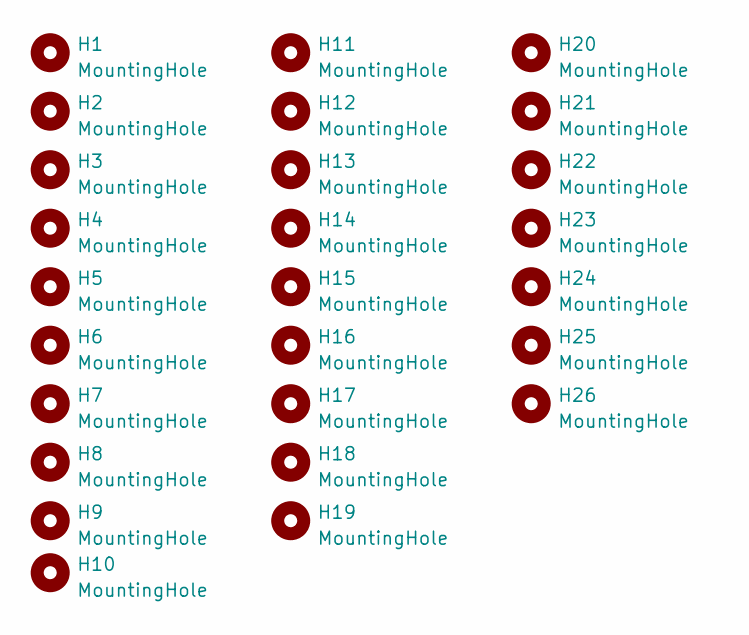
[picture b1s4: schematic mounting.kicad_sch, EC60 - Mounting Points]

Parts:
H1, H2, H3, H4, H5, H6, H7, H8, H9, H10, H11, H12, H13, H14, H15, H16, H17, H18, H19, H20, H21, H22, H23, H24, H25, H26: MountingHole; HOLE_M2
